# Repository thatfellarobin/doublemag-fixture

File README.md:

# doublemag-fixture
stuff for my double magnet fixture

## Working with z-offset
When  the sample is not at the same height as the magnets, i.e. there is an offset in the z axis, a different control mode is used.
Z offset at some key landmarks are listed:

- To bottom side of t slot aluminum: 33.66 mm
- To bottom side of t slot aluminum plus additional 1/16": 35.2 mm
- To bottom side of t slot aluminum plus additional 1/8": 36.84 mm

## Issues when running on ubuntu:

- https://askubuntu.com/questions/308128/failed-to-load-platform-plugin-xcb-while-launching-qt5-app-on-linux-without >> run `sudo apt-get install --reinstall libxcb-xinerama0`

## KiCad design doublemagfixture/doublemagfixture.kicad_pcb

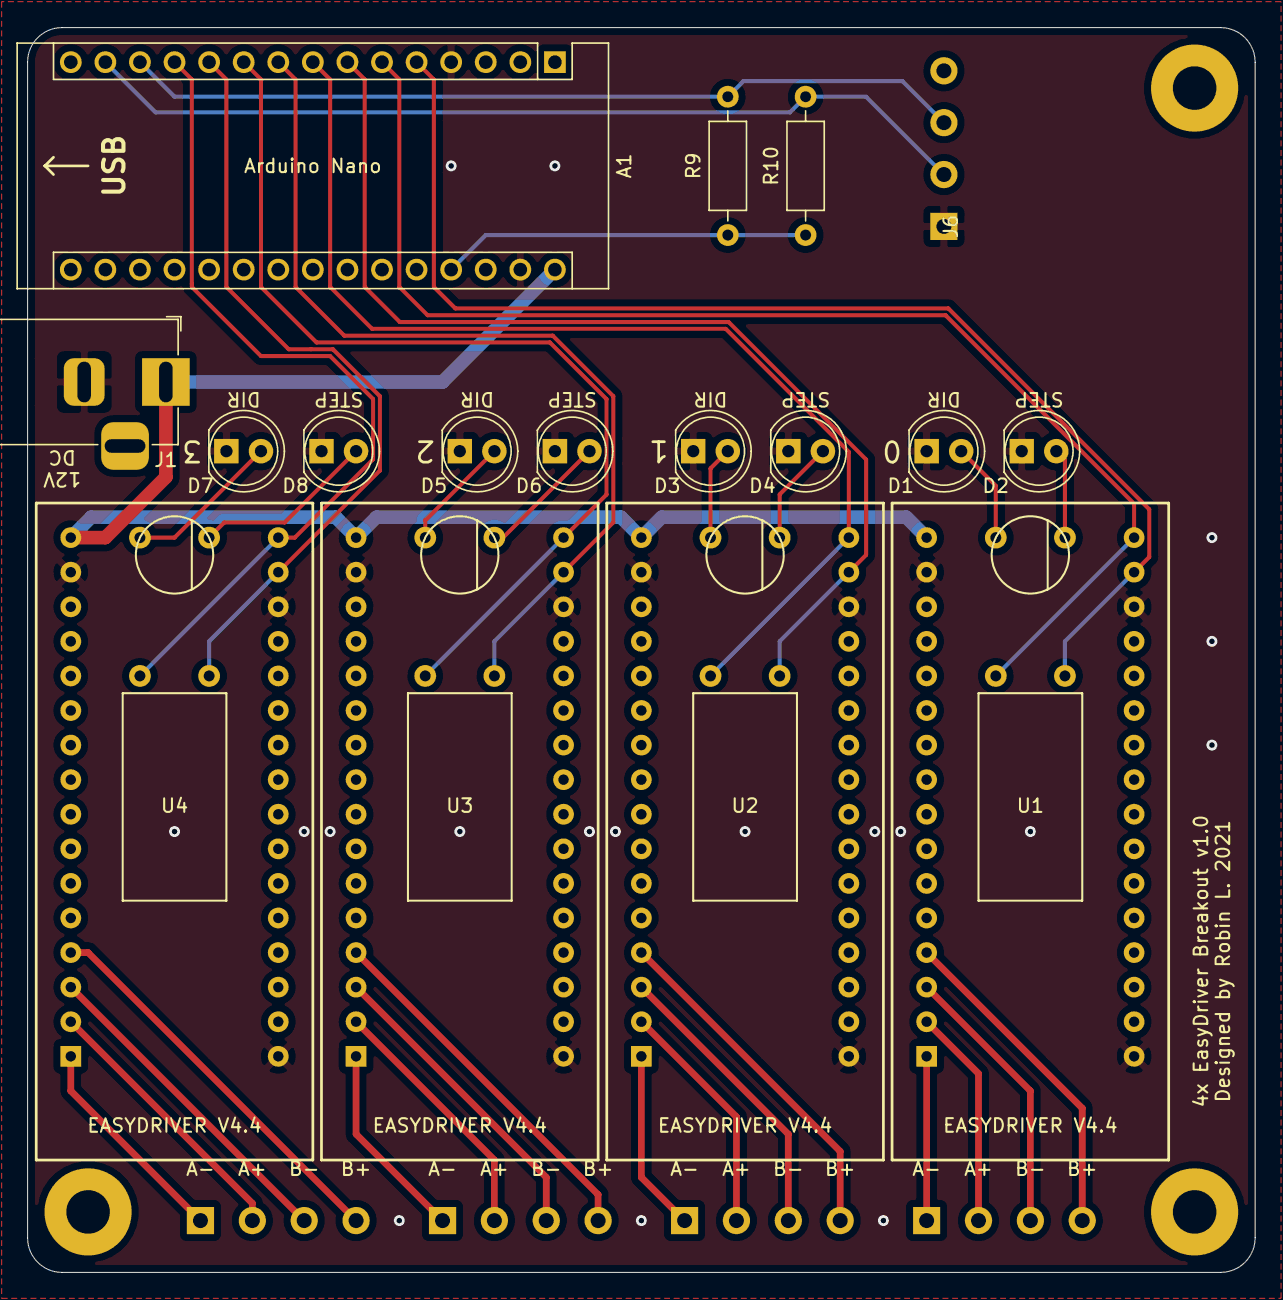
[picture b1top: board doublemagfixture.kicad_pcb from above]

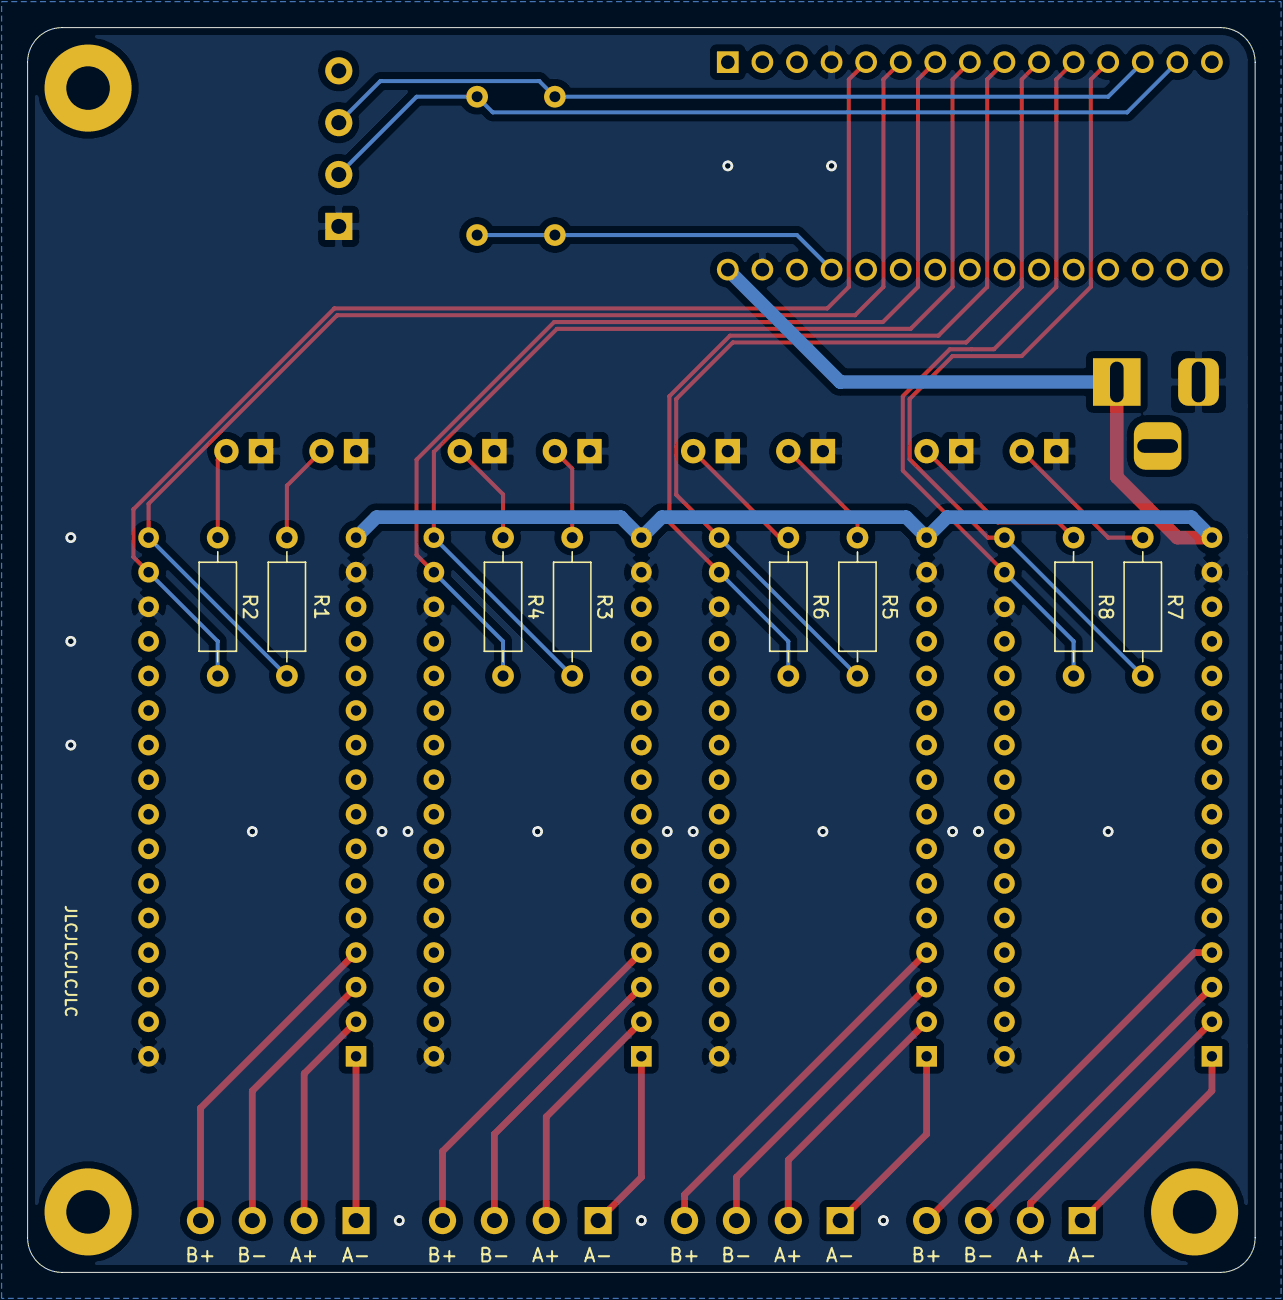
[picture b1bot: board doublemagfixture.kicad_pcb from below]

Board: 2 copper layers, 90.2 x 91.4 mm, 32 parts (8 on the bottom side), 37 nets.

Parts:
A1: Arduino_Nano_v3.x; Arduino_Nano
D1: DIR0; LED_D5.0mm
D2: STEP0; LED_D5.0mm
D3: DIR1; LED_D5.0mm
D4: STEP1; LED_D5.0mm
D5: DIR2; LED_D5.0mm
D6: STEP2; LED_D5.0mm
D7: DIR3; LED_D5.0mm
D8: STEP3; LED_D5.0mm
H1, H2, H3: MountingHole; MountingHole_3.2mm_M3_Pad
J1: Barrel_Jack_MountingPin; BarrelJack_Horizontal
J2, J3, J4, J5, J6: Screw_Terminal_01x04; CONN_1x4_3.81mm
R1, R2, R3, R4, R5, R6, R7, R8: 1k; R_Axial_DIN0207_L6.3mm_D2.5mm_P10.16mm_Horizontal
R9, R10: 10k; R_Axial_DIN0207_L6.3mm_D2.5mm_P10.16mm_Horizontal
U1, U2, U3, U4: easydriver_stepper_driver; easydriver_V44

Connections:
+5V: A1.27, R9.1, R10.1
+12V: A1.30, J1.1, U1.10, U2.10, U3.10, U4.10
/dir0: A1.6, R1.2, U1.11
/dir1: A1.8, R3.2, U2.11
/dir2: A1.10, R5.2, U3.11
/dir3: A1.12, R7.2, U4.11
/lim0: A1.13, J6.3, R9.2
/lim1: A1.14, J6.2, R10.2
/step0: A1.5, R2.2, U1.12
/step1: A1.7, R4.2, U2.12
/step2: A1.9, R6.2, U3.12
/step3: A1.11, R8.2, U4.12
GND: A1.4, A1.29, D1.1, D2.1, D3.1, D4.1, D5.1, D6.1, D7.1, D8.1, J1.2, J6.1, U1.9, U1.13, U1.17, U2.9, U2.13, U2.17, U3.9, U3.13, U3.17, U4.9, U4.13, U4.17
unnamed: D1.2, R1.1
unnamed: D2.2, R2.1
unnamed: D3.2, R3.1
unnamed: D4.2, R4.1
unnamed: D5.2, R5.1
unnamed: D6.2, R6.1
unnamed: D7.2, R7.1
unnamed: D8.2, R8.1
unnamed: J2.1, U1.1
unnamed: J2.2, U1.2
unnamed: J2.3, U1.3
unnamed: J2.4, U1.4
unnamed: J3.1, U2.1
unnamed: J3.2, U2.2
unnamed: J3.3, U2.3
unnamed: J3.4, U2.4
unnamed: J4.1, U3.1
unnamed: J4.2, U3.2
unnamed: J4.3, U3.3
unnamed: J4.4, U3.4
unnamed: J5.1, U4.1
unnamed: J5.2, U4.2
unnamed: J5.3, U4.3
unnamed: J5.4, U4.4

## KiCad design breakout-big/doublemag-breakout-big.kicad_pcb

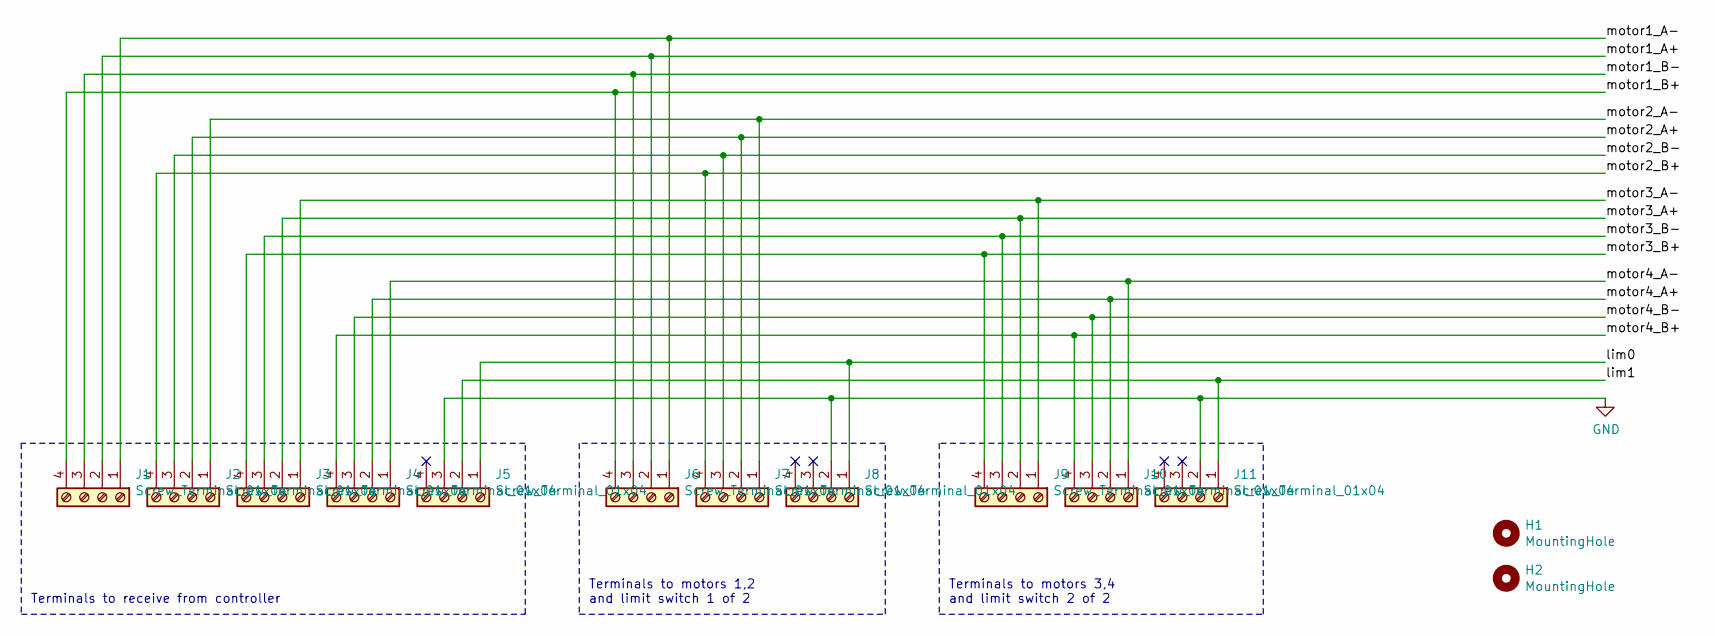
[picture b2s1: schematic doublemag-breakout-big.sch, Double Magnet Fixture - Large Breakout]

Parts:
H1, H2: MountingHole; MountingHole_3.2mm_M3_Pad
J1, J2, J3, J4, J5, J6, J7, J8, J9, J10, J11: Screw_Terminal_01x04; CONN_1x4_3.81mm

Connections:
/lim0: J5.1, J8.1
/lim1: J5.2, J11.1
/motor1_A+: J1.2, J6.2
/motor1_A-: J1.1, J6.1
/motor1_B+: J1.4, J6.4
/motor1_B-: J1.3, J6.3
/motor2_A+: J2.2, J7.2
/motor2_A-: J2.1, J7.1
/motor2_B+: J2.4, J7.4
/motor2_B-: J2.3, J7.3
/motor3_A+: J3.2, J9.2
/motor3_A-: J3.1, J9.1
/motor3_B+: J3.4, J9.4
/motor3_B-: J3.3, J9.3
/motor4_A+: J4.2, J10.2
/motor4_A-: J4.1, J10.1
/motor4_B+: J4.4, J10.4
/motor4_B-: J4.3, J10.3
GND: J5.3, J8.2, J11.2

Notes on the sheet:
Terminals to receive from controller
Terminals to motors 3,4 and limit switch 2 of 2
Terminals to motors 1,2 and limit switch 1 of 2

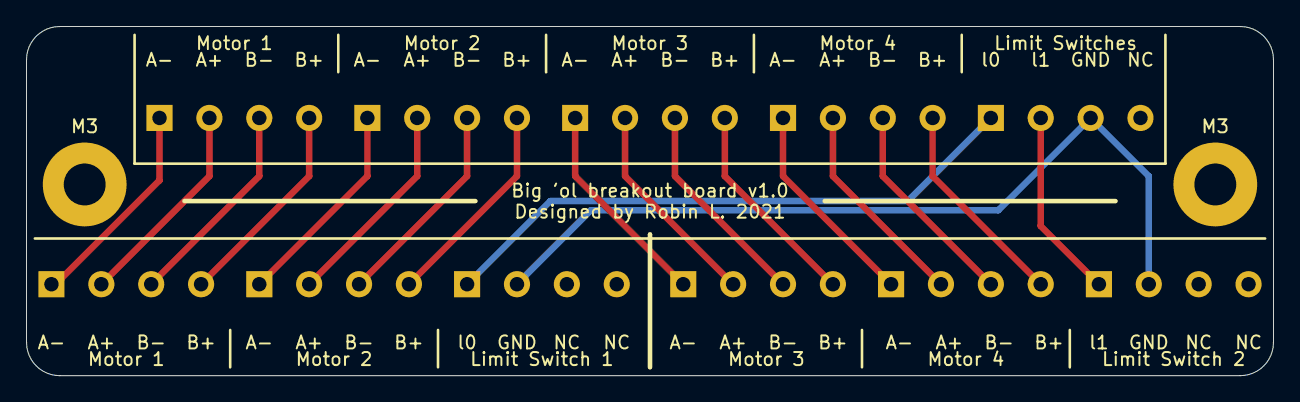
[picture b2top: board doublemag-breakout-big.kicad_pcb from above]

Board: 2 copper layers, 95.3 x 26.7 mm, 13 parts (0 on the bottom side), 19 nets.

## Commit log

2021-02-03 basic functionality to read mag sensor data
2021-02-04 beginning to reorganize
2021-02-09 I don't really know what I'm doing yet
2021-02-10 add ui file
2021-02-11 progress, I guess?
2021-02-11 some further work, architectural planning
2021-02-12 some more work on arduino sketch
2021-02-12 First go at all functions done
2021-02-12 slow progres
2021-02-18 continued updates
2021-02-18 added stop signal and fixed some bugs
2021-02-18 more edits
2021-02-19 approaching full functionality
2021-02-22 limit switch communications
2021-02-24 configure for pull-up resistors on lim switches
2021-02-24 started figuring out wiggle subthread
2021-02-24 debugging arduino sketch
2021-03-05 removed mag sensing from arduino sketch
2021-03-10 kinda working now
2021-03-22 added more buttons to ui
2021-04-14 updated .ui file to include data recording
2021-04-14 add stop data recording button
2021-04-14 separate stop recording button was not a good idea
2021-04-14 added data recording
2021-04-15 added wiggle mode, fixed a data recording bug
2021-04-15 updated UI for usability
2021-04-16 cleaned up data recording
2021-04-16 recording msgbox no longer plain txt
2021-04-21 adjusted manual stepping values
2021-04-21 small fixes
2021-04-21 increase angular max speed and accel
2021-04-21 minor fixes
2021-04-21 remove a print
2021-04-21 change font
2021-04-21 some code safety
2021-05-06 fixed wiggling frequency issue
2021-05-06 remove QThread import
2021-05-06 all fonts arial
2021-05-06 larger ui
2021-05-06 adjust wiggle frequency
2021-06-08 remove subthreads.py
    This file was the original plan for handling threaded tasks, but I ended
    up not needing it
2021-07-22 update gui for angle range 0 to 180 deg
2021-07-22 updates to adjust angle range
2021-07-27 added windows pc serial port
2021-07-29 GUI changes - visual
2021-07-29 autoselect serial port
2021-07-29 gui changes
    - changed sliders to spin box
2021-10-08 add kicad
2021-10-09 add kicad libs
2021-10-09 almost done pcb
2021-10-09 Final(?) pcb
2021-10-09 numbering fixes and wider traces on power line
2021-10-09 moved leds to front
2021-10-12 export gerber and drill files
2021-10-12 change LED to 5mm
2021-10-19 add breakout board and reconfigure main board
2021-10-22 change baud to 115200
2021-10-29 fix bug with incoming serial parsing
2021-12-16 add 3D mag work
2021-12-16 update filename
2021-12-20 first commit on branch
2021-12-20 working prototype?
2022-01-03 bugfix, match baud
2022-01-03 bugfix
    was erroneously interpolating on field strength instead of angle
2022-01-07 smoother control from bugfix in matlab code
2022-01-07 add more z offset files
2022-04-21 update wiggle mode
    wiggle mode now behaves more predictably. instead of trying to follow a
    sine wave, it moves between end stops with some pause at the limits.
    also updated the arduino code to push the motors faster, which allows
    for higher wiggle frequencies.
